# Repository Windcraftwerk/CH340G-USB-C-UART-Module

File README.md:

# CH340G-USB-C-UART-Module
USB type C UART Breakout Board with THT Components for easy home soldering using the CH340G in KiCad for practicing purposes.

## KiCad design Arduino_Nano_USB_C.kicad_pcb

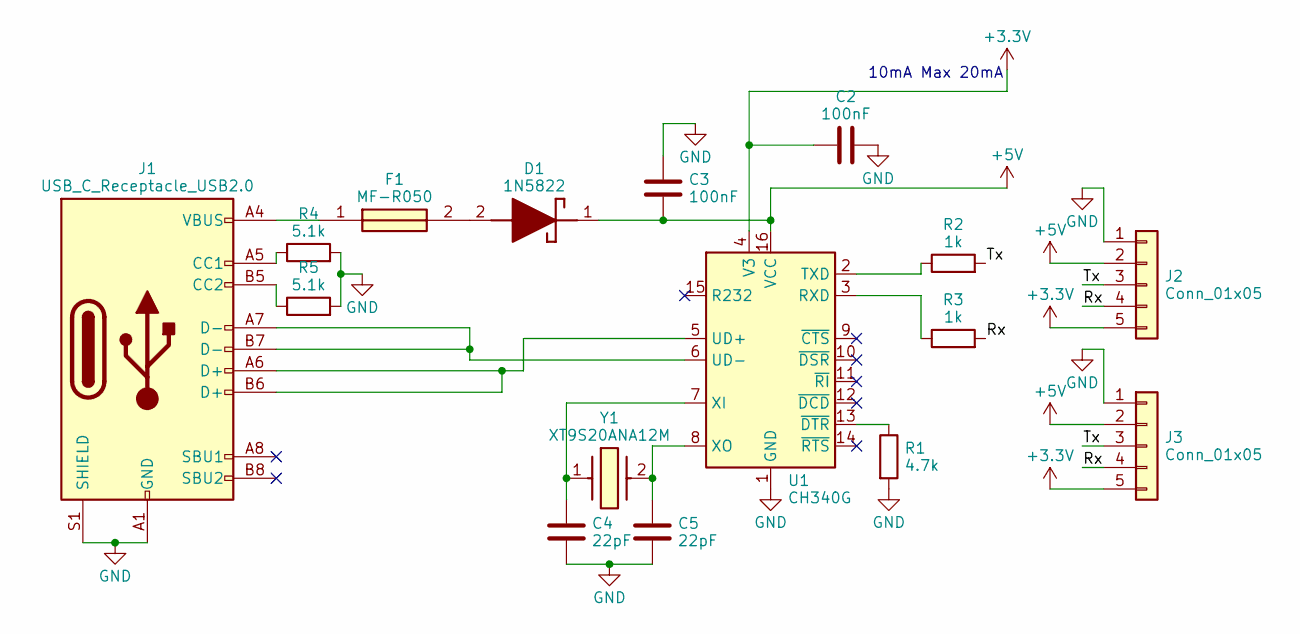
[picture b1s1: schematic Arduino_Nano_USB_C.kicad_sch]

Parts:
C2, C3: 100nF; CP_Radial_D5.0mm_P2.50mm
C4, C5: 22pF; CP_Radial_D5.0mm_P2.50mm
D1: 1N5822; DIOAD3070W130L950D530; Mouser Part Number 511-1N5822
F1: MF-R050; MFR050; Manufacturer_Part_Number MF-R050; Mouser Part Number 652-MFR050
J1: USB_C_Receptacle_USB2.0; USB_C_Receptacle_GCT_USB4085
J2, J3: Conn_01x05; PinHeader_1x05_P2.54mm_Vertical
R1: 4.7k; R_Axial_DIN0207_L6.3mm_D2.5mm_P7.62mm_Horizontal
R2, R3: 1k; R_Axial_DIN0207_L6.3mm_D2.5mm_P7.62mm_Horizontal
R4, R5: 5.1k; R_Axial_DIN0207_L6.3mm_D2.5mm_P7.62mm_Horizontal
U1: CH340G; SOIC-16_3.9x9.9mm_P1.27mm
Y1: XT9S20ANA12M; Mouser Part Number 73-XT49S1200-20

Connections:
+3.3V: C2.1, J2.5, J3.5, U1.4 (V3)
+5V: C3.1, D1.1 (K), J2.2, J3.2, U1.16 (VCC)
/Rx: J2.4, J3.4, R3.2
/Tx: J2.3, J3.3, R2.2
GND: C2.2, C3.2, C4.1, C5.1, J1.A1 (GND), J1.A12 (GND), J1.B1 (GND), J1.B12 (GND), J1.S1 (SHIELD), J2.1, J3.1, R1.2, R4.2, R5.2, U1.1 (GND)
unnamed: D1.2 (A), F1.2
unnamed: F1.1, J1.A4 (VBUS), J1.A9 (VBUS), J1.B4 (VBUS), J1.B9 (VBUS)
unnamed: J1.A5 (CC1), R4.1
unnamed: J1.B5 (CC2), R5.1
unnamed: R3.1, U1.3 (RXD)
unnamed: R2.1, U1.2 (TXD)
unnamed: J1.A6 (D+), J1.B6 (D+), U1.5 (UD+)
unnamed: J1.A7 (D-), J1.B7 (D-), U1.6 (UD-)
unnamed: C4.2, U1.7 (XI), Y1.1
unnamed: C5.2, U1.8 (XO), Y1.2
unnamed: R1.1, U1.13 (~DTR)

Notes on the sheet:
10mA Max 20mA

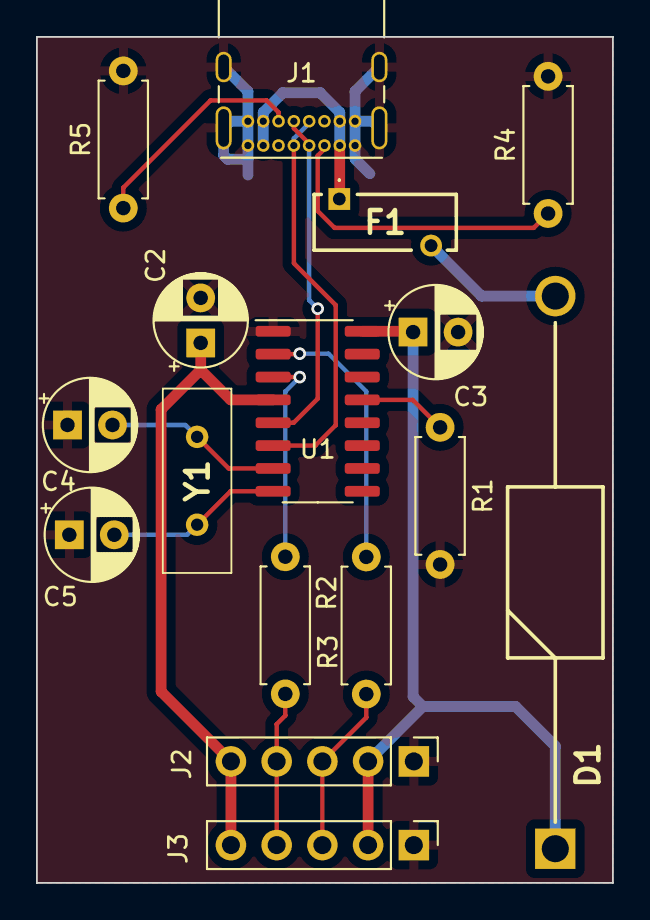
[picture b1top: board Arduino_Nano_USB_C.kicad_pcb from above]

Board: 2 copper layers, 32.0 x 47.0 mm, 16 parts (0 on the bottom side), 16 nets.

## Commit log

2025-05-26 Schematic and first Layout
2025-05-26 Finished Layout missing Border
2025-05-26 Adding Pictures
    Adding Pictures for easy visibility
2025-05-26 Update README.md
    Added pictures to readme.md
2025-05-26 Update README.md
    added %20 instead of spaces to images of readme
2025-05-27 Added Edge Cute. Cleaned up Ground Plane
2025-05-27 Update README.md
    Added description using KiCad
2025-10-01 Reordered Layout to keep decoupling capacitors close to chip. Updated pictures accordingly
